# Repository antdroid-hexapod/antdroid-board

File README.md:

# Antdroid Board
Shield for Arduino Mega used in [Antdroid](https://github.com/antdroid-hexapod/antdroid).

This is an alternative to the use of the SBEC, USB converter, LiPo alarm and Arduino Mega Shield protoboard for the robot [Antdroid](https://github.com/antdroid-hexapod/antdroid).

## Board features
* Two power supply of 5V 5A for servos.
* 19 servos pinheader connection
* Pin to control servos power supply
* One power suply of 5V 2A for Raspberry Pi
* Logic level converter to allow serial pin connection between Arduino and Raspberry Pi
* Analog input to measure battery voltage
* Optional I2C connection

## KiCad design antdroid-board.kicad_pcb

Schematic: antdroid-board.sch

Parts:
C1, C2, C3, C4: 470µF/25V; C_Radial_D10_L13_P5
C5, C6: 0.47µF; C_Disc_D6_P5
C7: 100µF/25V; c_elec_6.3x7.7
C8, C9, C10: 10nF; C_0603_HandSoldering
C11, C12: 1000µF/50V; C_Radial_D12.5_L25_P5
C13: 100µF/16V; C_Radial_D5_L11_P2
D1, D2: MBR745G; Diode_TO-220_Vertical
D3: MBRS340; Diode-DO-214AB_Handsoldering
D4, D5: LED; LED-0603
JP1, JP2, JP3, JP4, JP5, JP6, JP7, JP8, JP9, JP10, JP11, JP12, JP13, JP14, JP15, JP16, JP17, JP18, JP21: PINHD-1X3_2.54; Pin_Header_Straight_1x03
JP19: PINHD-1X5; Pin_Header_Straight_1x05
JP20: PINHD-1X4_2.54; Pin_Header_Straight_1x04
L1, L2: 15µH/5.8A; SELF-WE-PD-XXL
L3: 47µH/2A; SELF-WE-PD-XXL
P1, P2: CONN_01X01; 1pin
Q1, Q2: BSS138; SOT-23
R1: 33K; R_0603_HandSoldering
R2, R3, R4, R5, R6: 10K; R_0603_HandSoldering
R7, R8: 1KΩ; R_0603_HandSoldering
SHIELD1: ARDUINO_MEGA_SHIELD; ArduinoMegaShield
U1, U2: LM2678T-5.0; TO-220-7C
U3: LM2675M-5; AB2_SO08

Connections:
+3V3: JP19.3, Q1.1 (G), Q2.1 (G), R5.1, R6.1
+5V: C13.1, JP19.2, JP20.4, L3.1, U3.4 (FB)
+5VA: C11.1, JP1.2, JP2.2, JP3.2, JP4.2, JP5.2, JP6.2, JP7.2, JP8.2, JP9.2, JP21.2, L1.1, R7.1, U1.6 (FB)
+5VD: C12.1, JP10.2, JP11.2, JP12.2, JP13.2, JP14.2, JP15.2, JP16.2, JP17.2, JP18.2, L2.1, R8.1, U2.6 (FB)
+5VP: R3.1, R4.1, SHIELD1.5V_4
/AUX: JP21.3, SHIELD1.34 (PC3)
/LFC: JP1.3, SHIELD1.22 (PA0)
/LFF: JP2.3, SHIELD1.23 (PA1)
/LFT: JP3.3, SHIELD1.24 (PA2)
/LMC: JP4.3, SHIELD1.25 (PA3)
/LMF: JP5.3, SHIELD1.26 (PA4)
/LMT: JP6.3, SHIELD1.27 (PA5)
/LRC: JP7.3, SHIELD1.28 (PA6)
/LRF: JP8.3, SHIELD1.29 (PA7)
/LRT: JP9.3, SHIELD1.30 (PC7)
/RFC: JP10.3, SHIELD1.53 (PB0_(SS))
/RFF: JP11.3, SHIELD1.52 (PB1_(SCK))
/RFT: JP12.3, SHIELD1.51 (PB2_(MOSI))
/RMC: JP13.3, SHIELD1.50 (PB3_(MISO))
/RMF: JP14.3, SHIELD1.49 (PL0)
/RMT: JP15.3, SHIELD1.48 (PL1)
/RPI_RX: JP19.5, Q1.2 (S), R5.2
/RPI_TX: JP19.4, Q2.2 (S), R6.2
/RRC: JP16.3, SHIELD1.47 (PL2)
/RRF: JP17.3, SHIELD1.46 (PL3)
/RRT: JP18.3, SHIELD1.45 (PL4)
/RX0: Q2.3 (D), R4.2, SHIELD1.0 (RX0)
/SERVO_ON: SHIELD1.13, U1.7 (ON/~OFF), U2.7 (ON/~OFF)
/TX0: Q1.3 (D), R3.2, SHIELD1.1 (TX0)
GND: C1.2, C2.2, C3.2, C4.2, C5.2, C6.2, C7.2, C11.2, C12.2, C13.2, D1.2, D2.2, D3.2, D4.1 (K), D5.1 (K), JP1.1, JP2.1, JP3.1, JP4.1, JP5.1, JP6.1, JP7.1, JP8.1, JP9.1, JP10.1, JP11.1, JP12.1, JP13.1, JP14.1, JP15.1, JP16.1, JP17.1, JP18.1, JP19.1, JP20.1, JP21.1, P1.1, R2.2, SHIELD1.GND1, SHIELD1.GND2, SHIELD1.GND3, SHIELD1.GND4, SHIELD1.GND5, U1.4 (GND), U2.4 (GND), U3.6 (GND)
unnamed: C8.1, U1.3 (CB)
unnamed: C8.2, D1.1, L1.2, U1.1 (VSW)
unnamed: C9.1, U2.3 (CB)
unnamed: C9.2, D2.1, L2.2, U2.1 (VSW)
unnamed: C10.1, D3.1, L3.2, U3.8 (VSW)
unnamed: C10.2, U3.1 (CB)
unnamed: D4.2 (A), R7.2
unnamed: D5.2 (A), R8.2
unnamed: JP20.2, SHIELD1.20 (SDA)
unnamed: JP20.3, SHIELD1.21 (SCL)
unnamed: R1.2, R2.1, SHIELD1.AD0
VCC: C1.1, C2.1, C3.1, C4.1, C5.1, C6.1, C7.1, P2.1, R1.1, SHIELD1.V_IN, U1.2 (VIN), U2.2 (VIN), U3.7 (VIN)

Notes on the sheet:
Serial Raspberry Pi
Raspberry Pi power supply
Servos power supply
Servo power LEDs
Left front leg
Left middle leg
Left rear leg
Right front leg
Right middle leg
Right rear leg
Battery connector
Raspberry Pi connector
Arduino Mega shield
Aux servo

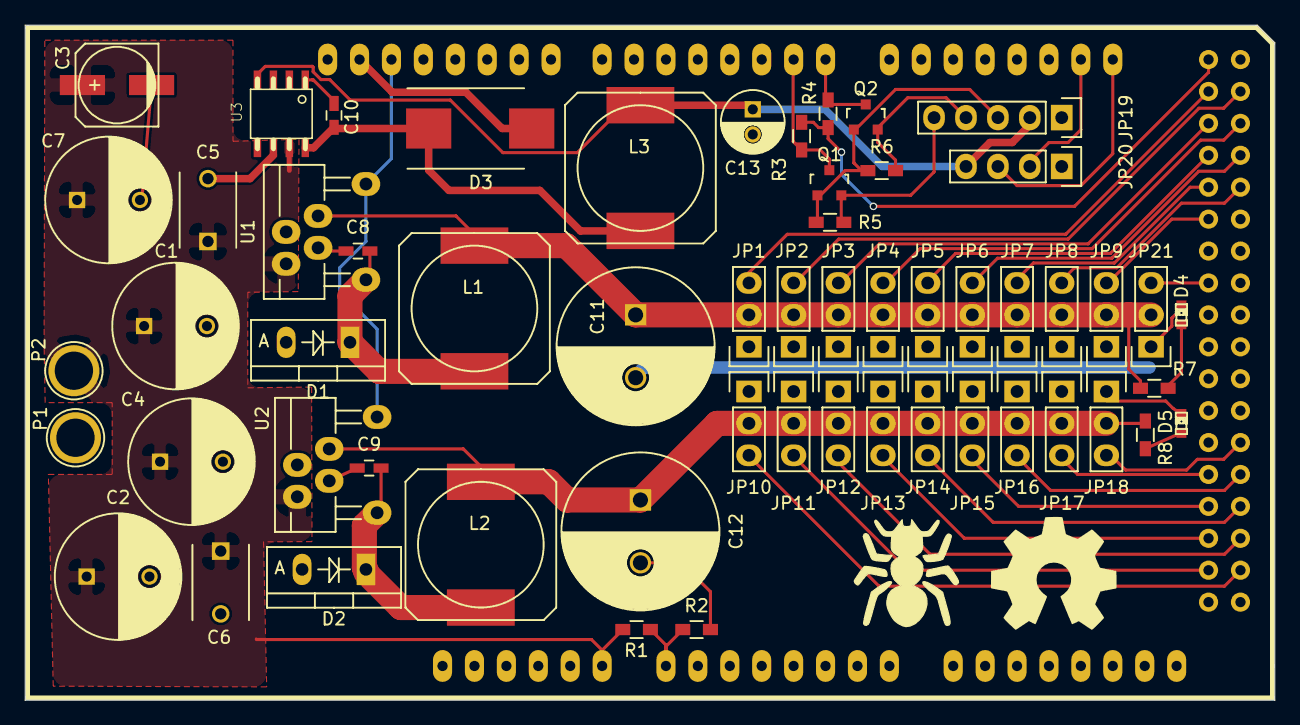
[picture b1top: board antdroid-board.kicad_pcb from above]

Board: 2 copper layers, 99.4 x 53.7 mm, 58 parts (0 on the bottom side), 42 nets.

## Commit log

2015-07-06 Added Servo Power Supply
2015-07-07 Change power supply to LM26XX
2015-07-07 Added JP of servos
2015-07-07 Added PWR_FLAGS
2015-07-09 PSU components fixed and some datasheet added
2015-07-09 Change all 5V and 3V3 connections, resize papper
2015-07-09 Added schematic pdf
2015-07-09 Finish footprint asign
2015-07-09 Starting place components, some fingerprints fixed
2015-07-11 All components positioned and design rules almost done
2015-07-11 Adding edges
2015-07-12 Almost tracked and logo added
2015-07-12 Finally tracked
2015-07-12 Create lib dir
2015-07-13 Relocate libs and footprints
2015-07-13 Fixed pin number TO-220-7C
2015-07-13 Added separation for heatsinks and outputs
2015-07-13 Supplier ref added.
2015-07-13 Remove temporal and cache files
2015-07-13 Fixed lib, missing elements.
2015-07-13 Fixed library components.
2015-07-13 Added LED smd
2015-07-13 Update some resistors
2015-07-13 Added aux pin. Finished?
2015-07-13 Added render views.
2015-07-13 Update reference 31.2K resistor
2015-07-13 Remove old BOM
2015-07-14 All revised, final release
2015-07-14 Final release. Updated README Added board name in bottom silkscreen
2015-07-14 Added license
2015-07-15 Updated Resistor 31.2k to 33k
2015-07-15 Fixed bottom gnd track
2015-07-16 Fixed somo references.
2015-07-20 Fixed image.
2015-09-29 LED resistor change to 1K
2015-09-29 Fixed silkscreen
2015-10-01 Fixed output capacitors
2015-10-01 Update output pdf
2015-10-02 Antdroid Board images upload.
2016-01-28 Removed image.
